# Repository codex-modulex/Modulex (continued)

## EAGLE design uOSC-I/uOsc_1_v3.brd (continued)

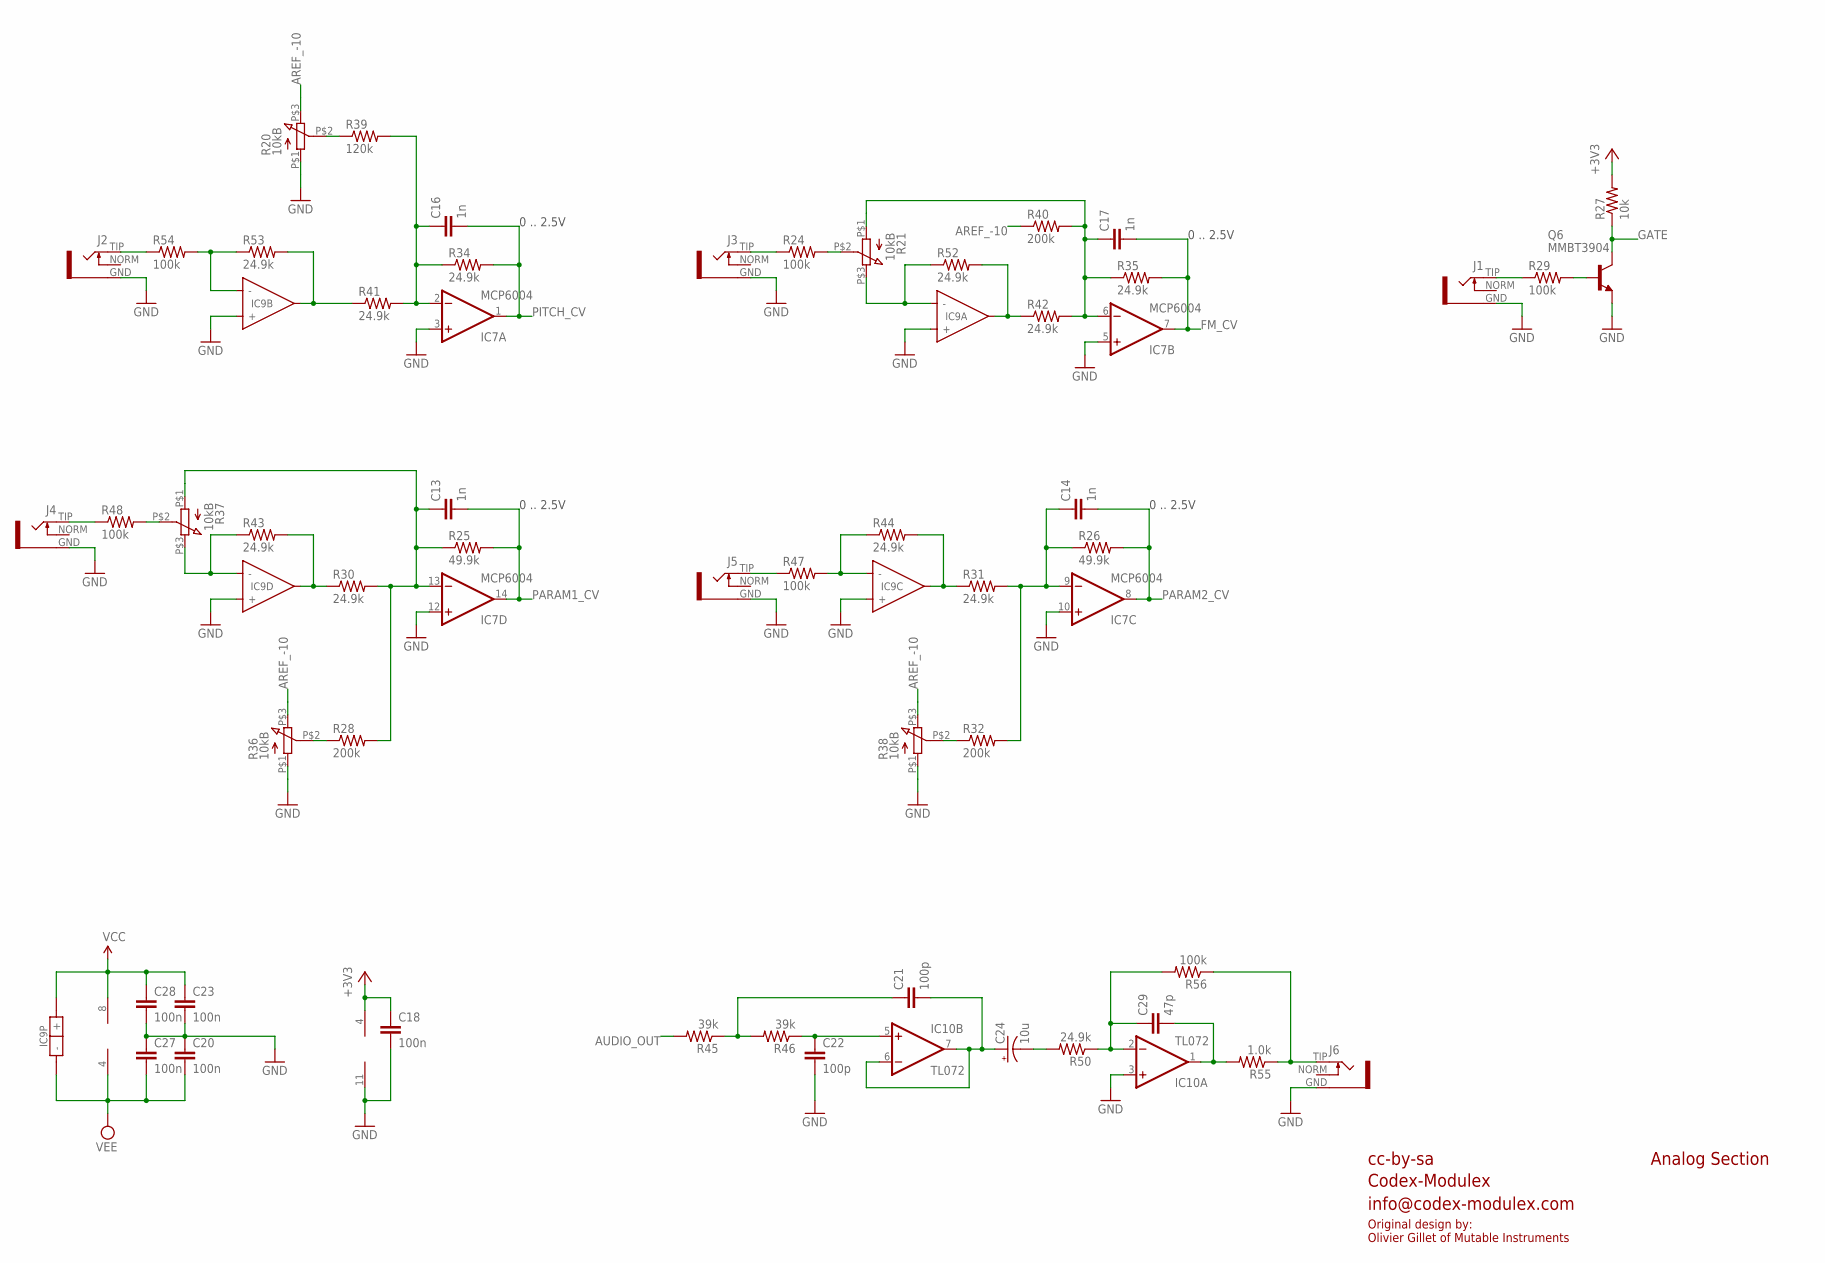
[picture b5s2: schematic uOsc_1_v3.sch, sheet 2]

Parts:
C13, C14, C16, C17: 1n; PARTS_AMAN_RESISTOR_0603
C18, C20, C23, C27, C28: 100n; PARTS_AMAN_RESISTOR_0603
C21, C22: 100p; PARTS_AMAN_RESISTOR_0603
C24: 10u; PANASONIC_B
C29: 47p; PARTS_AMAN_RESISTOR_0603
IC7: MCP6004; SO14
IC9: TL074; UBRAIDS_SE_TSSOP-14
IC10: TL072; SO08
J1, J2, J3, J4, J5, J6: S_JACK_S2_INV
Q6: MMBT3904; SOT23-BEC
R20, R21, R36, R37, R38: 10kB; Q-POT2
R24, R29, R47, R48, R54, R56: 100k; PARTS_AMAN_RESISTOR_0603
R25, R26: 49.9k; PARTS_AMAN_RESISTOR_0603
R27: 10k; PARTS_AMAN_RESISTOR_0603
R28, R32, R40: 200k; PARTS_AMAN_RESISTOR_0603
R30, R31, R34, R35, R41, R42, R43, R44, R50, R52, R53: 24.9k; PARTS_AMAN_RESISTOR_0603
R39: 120k; PARTS_AMAN_RESISTOR_0603
R45, R46: 39k; PARTS_AMAN_RESISTOR_0603
R55: 1.0k; PARTS_AMAN_RESISTOR_0603

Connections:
+3V3: C18.1, IC7.4 (V+), R27.2; also elsewhere on the board
AREF_-10: R20.P$3 (3), R36.P$3 (3), R38.P$3 (3), R40.1; also elsewhere on the board
AUDIO_OUT: R45.2; also elsewhere on the board
FM_CV: C17.2, IC7.7 (OUT), R35.2; also elsewhere on the board
GATE: Q6.C, R27.1; also elsewhere on the board
GND: C18.2, C20.1, C22.2, C23.2, C27.1, C28.2, IC7.3 (+IN), IC7.5 (+IN), IC7.10 (+IN), IC7.11 (V-), IC7.12 (+IN), IC9.3 (+), IC9.5 (+), IC9.10 (+), IC9.12 (+), IC10.3 (+IN), J1.GND, J2.GND, J3.GND, J4.GND, J5.GND, J6.GND, Q6.E, R20.P$1 (1), R36.P$1 (1), R38.P$1 (1); also elsewhere on the board
unnamed: IC9.7 (OUT), R41.1, R53.2
unnamed: R20.P$2 (2), R39.1
unnamed: J2.TIP, R54.1
unnamed: C16.1, IC7.2 (-IN), R34.1, R39.2, R41.2
unnamed: IC9.6 (-), R53.1, R54.2
unnamed: J3.TIP, R24.1
unnamed: J4.TIP, R48.1
unnamed: R21.P$2 (2), R24.2
unnamed: IC9.13 (-), R37.P$3 (3), R43.1
unnamed: IC9.14 (OUT), R30.1, R43.2
unnamed: IC9.2 (-), R21.P$3 (3), R52.1
unnamed: IC9.1 (OUT), R42.1, R52.2
unnamed: C17.1, IC7.6 (-IN), R21.P$1 (1), R35.1, R40.2, R42.2
unnamed: J1.TIP, R29.1
unnamed: IC9.8 (OUT), R31.1, R44.2
unnamed: C13.1, IC7.13 (-IN), R25.1, R28.2, R30.2, R37.P$1 (1)
unnamed: J5.TIP, R47.1
unnamed: R28.1, R36.P$2 (2)
unnamed: R37.P$2 (2), R48.2
unnamed: IC9.9 (-), R44.1, R47.2
unnamed: R32.1, R38.P$2 (2)
unnamed: Q6.B, R29.2
unnamed: C21.2, C24.+, IC10.6 (-IN), IC10.7 (OUT)
unnamed: C24.-, R50.2
unnamed: C22.1, IC10.5 (+IN), R46.1
unnamed: C14.1, IC7.9 (-IN), R26.1, R31.2, R32.2
unnamed: C21.1, R45.1, R46.2
unnamed: J6.TIP, R55.1, R56.1
unnamed: C29.2, IC10.1 (OUT), R55.2
unnamed: C29.1, IC10.2 (-IN), R50.1, R56.2
PARAM1_CV: C13.2, IC7.14 (OUT), R25.2; also elsewhere on the board
PARAM2_CV: C14.2, IC7.8 (OUT), R26.2; also elsewhere on the board
PITCH_CV: C16.2, IC7.1 (OUT), R34.2; also elsewhere on the board
VCC: C23.1, C28.1, IC9.4 (+), IC10.8 (V+); also elsewhere on the board
VEE: C20.2, C27.2, IC9.11 (-), IC10.4 (V-); also elsewhere on the board

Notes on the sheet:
cc-by-sa
Codex-Modulex
info@codex-modulex.com
Analog Section
0 .. 2.5V
Original design by: Olivier Gillet of Mutable Instruments

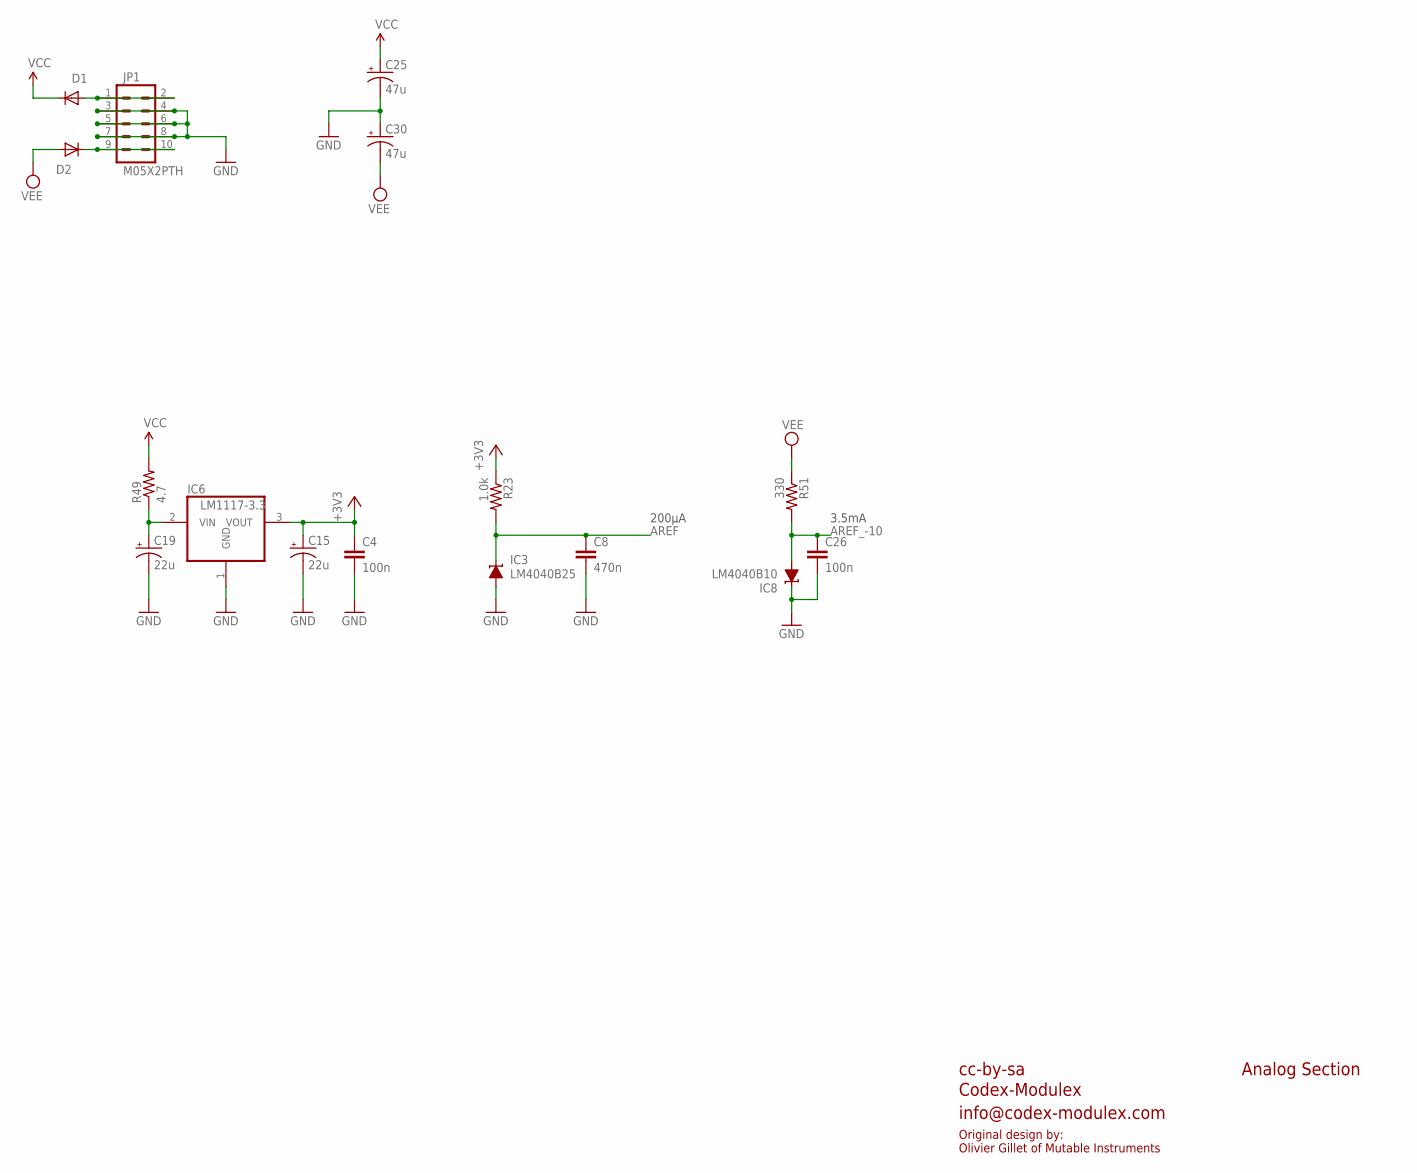
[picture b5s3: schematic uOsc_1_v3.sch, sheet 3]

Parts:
C4, C26: 100n; PARTS_AMAN_RESISTOR_0603
C8: 470n; PARTS_AMAN_RESISTOR_0603
C15, C19: 22u; PANASONIC_C
C25, C30: 47u; PANASONIC_D
D1, D2: 1N5819HW; SOD123
IC3: LM4040B25; DBZ_R-PDSO-G3
IC6: LM1117-3.3; TO252
IC8: LM4040B10; DBZ_R-PDSO-G3
JP1: M05X2PTH; AVR_ICSP
R23: 1.0k; PARTS_AMAN_RESISTOR_0603
R49: 4.7; R1206
R51: 330; PARTS_AMAN_RESISTOR_0603

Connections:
+3V3: C4.1, C15.+, IC6.3 (VOUT), R23.1; also elsewhere on the board
AREF: C8.1, IC3.1 (C), R23.2; also elsewhere on the board
AREF_-10: C26.1, IC8.2 (A), R51.2; also elsewhere on the board
GND: C4.2, C8.2, C15.-, C19.-, C25.-, C26.2, C30.+, IC3.2 (A), IC6.1 (GND), IC8.1 (C), JP1.3, JP1.4, JP1.5, JP1.6, JP1.7, JP1.8; also elsewhere on the board
unnamed: C19.+, IC6.2 (VIN), R49.1
unnamed: D1.A, JP1.1, JP1.2
unnamed: D2.C, JP1.9, JP1.10
VCC: C25.+, D1.C, R49.2; also elsewhere on the board
VEE: C30.-, D2.A, R51.1; also elsewhere on the board

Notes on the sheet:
3.5mA
200µA
cc-by-sa
Codex-Modulex
info@codex-modulex.com
Analog Section
Original design by: Olivier Gillet of Mutable Instruments

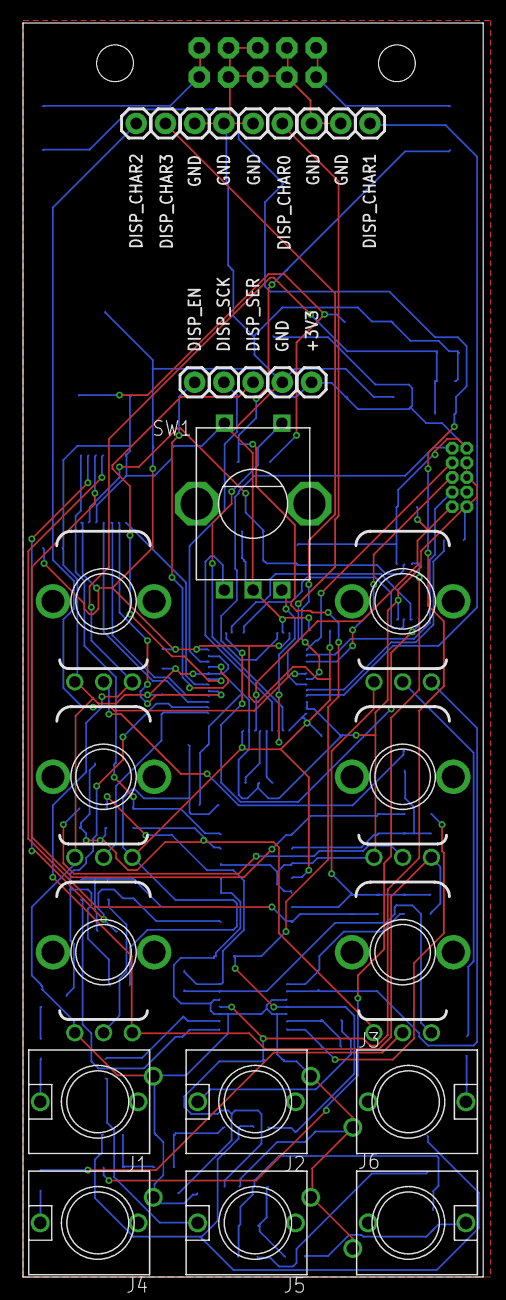
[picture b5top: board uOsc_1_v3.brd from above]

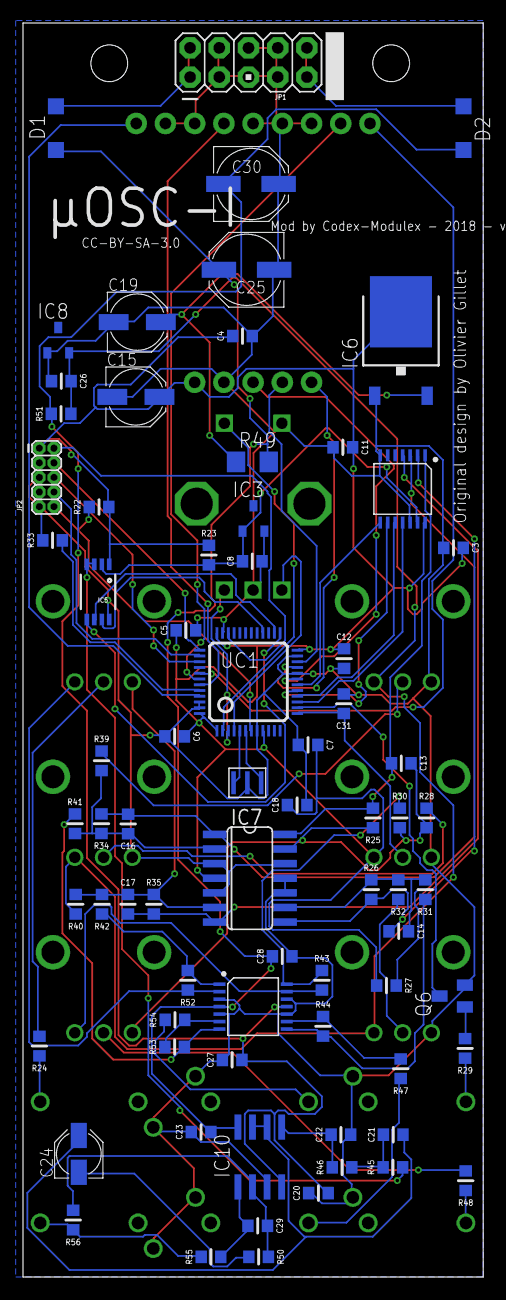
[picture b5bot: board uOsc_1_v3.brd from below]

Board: 2 copper layers, 40.0 x 109.0 mm, 101 parts (74 on the bottom side), 71 nets.

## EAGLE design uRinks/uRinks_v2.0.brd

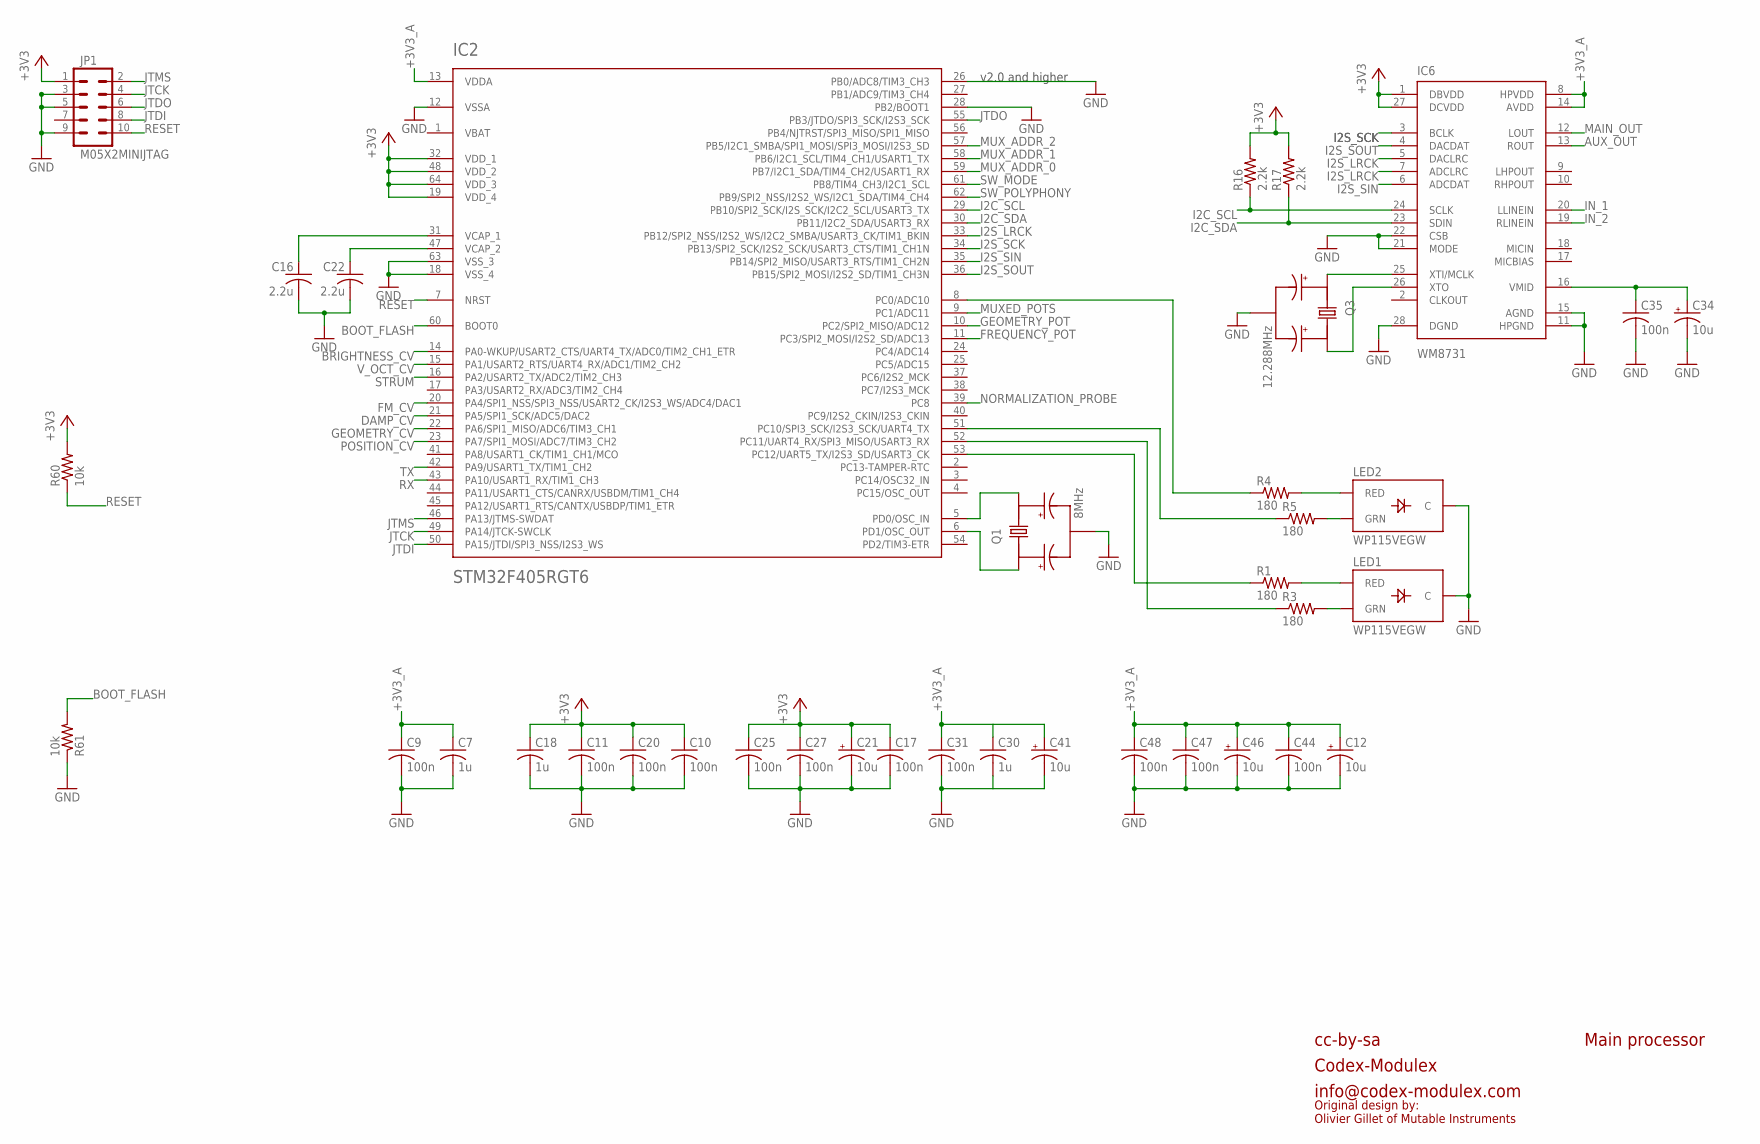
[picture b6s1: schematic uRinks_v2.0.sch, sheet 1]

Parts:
C7, C18, C30: 1u; C0603
C9, C10, C11, C17, C20, C25, C27, C31, C35, C44, C47, C48: 100n; C0603
C12, C21, C34, C41, C46: 10u; PANASONIC_A
C16, C22: 2.2u; C0805
IC2: STM32F405RGT6; TQFP-10X10-64
IC6: WM8731; SSOP28
JP1: M05X2MINIJTAG; 2X5-1.27
LED1, LED2: WP115VEGW; LED-BICOLOR-THROUGHHOLE
Q1: 8MHz; INSTRUO_CRYSTAL_SMALLER
Q3: 12.288MHz; INSTRUO_CRYSTAL_SMALLER
R1, R3, R4, R5: 180; R0603
R16, R17: 2.2k; R0603
R60, R61: 10k; R0603

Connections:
+3V3: C10.1, C11.1, C17.1, C18.1, C20.1, C21.+, C25.1, C27.1, IC2.19 (VDD_4), IC2.32 (VDD_1), IC2.48 (VDD_2), IC2.64 (VDD_3), IC6.1 (DBVDD), IC6.27 (DCVDD), JP1.1, R16.2, R17.2, R60.2; also elsewhere on the board
+3V3_A: C7.1, C9.1, C12.+, C30.1, C31.1, C41.+, C44.1, C46.+, C47.1, C48.1, IC2.13 (VDDA), IC6.8 (HPVDD), IC6.14 (AVDD); also elsewhere on the board
AUX_OUT: IC6.13 (ROUT); also elsewhere on the board
BOOT_FLASH: IC2.60 (BOOT0), R61.2
BRIGHTNESS_CV: IC2.14 (PA0-WKUP/USART2_CTS/UART4_TX/ADC0/TIM2_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); also elsewhere on the board
DAMP_CV: IC2.21 (PA5/SPI1_SCK/ADC5/DAC2); also elsewhere on the board
FM_CV: IC2.20 (PA4/SPI1_NSS/SPI3_NSS/USART2_CK/I2S3_WS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); also elsewhere on the board
FREQUENCY_POT: IC2.11 (PC3/SPI2_MOSI/I2S2_SD/ADC13); also elsewhere on the board
GEOMETRY_CV: IC2.22 (PA6/SPI1_MISO/ADC6/TIM3_CH1); also elsewhere on the board
GEOMETRY_POT: IC2.10 (PC2/SPI2_MISO/ADC12); also elsewhere on the board
GND: C7.2, C9.2, C10.2, C11.2, C12.-, C16.2, C17.2, C18.2, C20.2, C21.-, C22.2, C25.2, C27.2, C30.2, C31.2, C34.-, C35.2, C41.-, C44.2, C46.-, C47.2, C48.2, IC2.12 (VSSA), IC2.18 (VSS_4), IC2.26 (PB0/ADC8/TIM3_CH3), IC2.28 (PB2/BOOT1), IC2.63 (VSS_3), IC6.11 (HPGND), IC6.15 (AGND), IC6.21 (MODE), IC6.22 (CSB), IC6.28 (DGND), JP1.3, JP1.5, JP1.9, LED1.2 (C), LED2.2 (C), Q1.GND, Q3.GND, R61.1; also elsewhere on the board
I2C_SCL: IC2.29 (PB10/SPI2_SCK/I2S_SCK/I2C2_SCL/USART3_TX), IC6.24 (SCLK), R16.1
I2C_SDA: IC2.30 (PB11/I2C2_SDA/USART3_RX), IC6.23 (SDIN), R17.1
I2S_LRCK: IC2.33 (PB12/SPI2_NSS/I2S2_WS/I2C2_SMBA/USART3_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), IC6.5 (DACLRC), IC6.7 (ADCLRC)
I2S_SCK: IC2.34 (PB13/SPI2_SCK/I2S2_SCK/USART3_CTS/TIM1_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), IC6.3 (BCLK)
I2S_SIN: IC2.35 (PB14/SPI2_MISO/USART3_RTS/TIM1_CH2N), IC6.6 (ADCDAT)
I2S_SOUT: IC2.36 (PB15/SPI2_MOSI/I2S2_SD/TIM1_CH3N), IC6.4 (DACDAT)
IN_1: IC6.20 (LLINEIN); also elsewhere on the board
IN_2: IC6.19 (RLINEIN); also elsewhere on the board
JTCK: IC2.49 (PA14/JTCK-SWCLK), JP1.4
JTDI: IC2.50 (PA15/JTDI/SPI3_NSS/I2S3_WS), JP1.8
JTDO: IC2.55 (PB3/JTDO/SPI3_SCK/I2S3_SCK), JP1.6
JTMS: IC2.46 (PA13/JTMS-SWDAT), JP1.2
MAIN_OUT: IC6.12 (LOUT); also elsewhere on the board
MUXED_POTS: IC2.9 (PC1/ADC11); also elsewhere on the board
MUX_ADDR_0: IC2.59 (PB7/I2C1_SDA/TIM4_CH2/USART1_RX); also elsewhere on the board
MUX_ADDR_1: IC2.58 (PB6/I2C1_SCL/TIM4_CH1/USART1_TX); also elsewhere on the board
MUX_ADDR_2: IC2.57 (PB5/I2C1_SMBA/SPI1_MOSI/SPI3_MOSI/I2S3_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); also elsewhere on the board
unnamed: IC2.6 (PD1/OSC_OUT), Q1.X1
unnamed: IC2.5 (PD0/OSC_IN), Q1.X2
unnamed: LED1.3 (RED), R1.2
unnamed: C22.1, IC2.47 (VCAP_2)
unnamed: C34.+, C35.1, IC6.16 (VMID)
unnamed: C16.1, IC2.31 (VCAP_1)
unnamed: LED1.1 (GRN), R3.2
unnamed: LED2.3 (RED), R4.2
unnamed: LED2.1 (GRN), R5.2
unnamed: IC2.52 (PC11/UART4_RX/SPI3_MISO/USART3_RX), R3.1
unnamed: IC2.8 (PC0/ADC10), R4.1
unnamed: IC6.25 (XTI/MCLK), Q3.X1
unnamed: IC6.26 (XTO), Q3.X2
unnamed: IC2.53 (PC12/UART5_TX/I2S3_SD/USART3_CK), R1.1
unnamed: IC2.51 (PC10/SPI3_SCK/I2S3_SCK/UART4_TX), R5.1
NORMALIZATION_PROBE: IC2.39 (PC8); also elsewhere on the board
POSITION_CV: IC2.23 (PA7/SPI1_MOSI/ADC7/TIM3_CH2); also elsewhere on the board
RESET: IC2.7 (NRST), JP1.10, R60.1
RX: IC2.43 (PA10/USART1_RX/TIM1_CH3)
STRUM: IC2.16 (PA2/USART2_TX/ADC2/TIM2_CH3); also elsewhere on the board
SW_MODE: IC2.61 (PB8/TIM4_CH3/I2C1_SCL); also elsewhere on the board
SW_POLYPHONY: IC2.62 (PB9/SPI2_NSS/I2S2_WS/I2C1_SDA/TIM4_CH4); also elsewhere on the board
TX: IC2.42 (PA9/USART1_TX/TIM1_CH2)
VBAT: IC2.1 (VBAT)
V_OCT_CV: IC2.15 (PA1/USART2_RTS/UART4_RX/ADC1/TIM2_CH2); also elsewhere on the board

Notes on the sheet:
cc-by-sa
Codex-Modulex
info@codex-modulex.com
Main processor
v2.0 and higher
Original design by: Olivier Gillet of Mutable Instruments

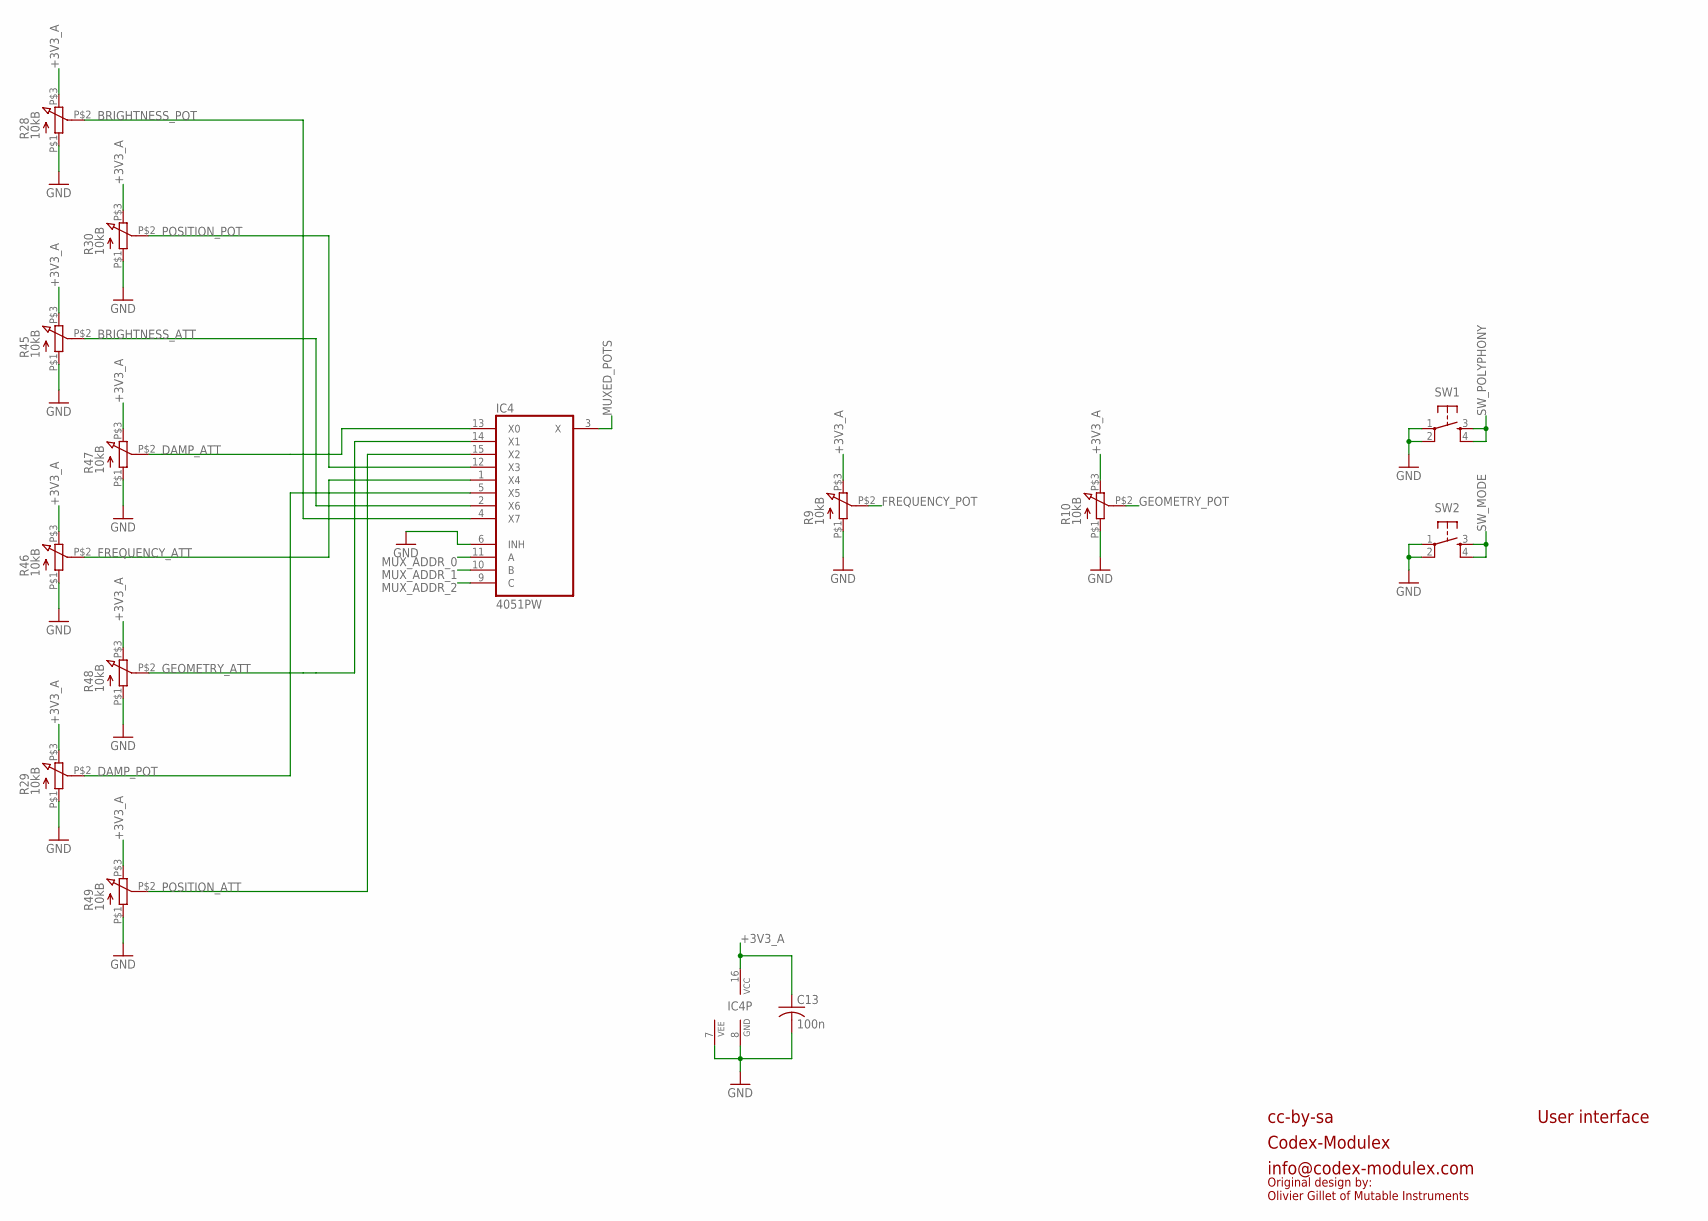
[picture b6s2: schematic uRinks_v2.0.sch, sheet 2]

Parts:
C13: 100n; C0603
IC4: 4051PW; TSSOP16
R9, R10, R28, R29, R30, R45, R46, R47, R48, R49: 10kB; INSTRUO_Q-POT2
SW1, SW2: TAC_SWITCHPTH; TACTILE-PTH

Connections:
+3V3_A: C13.1, IC4.16 (VCC), R9.P$3 (3), R10.P$3 (3), R28.P$3 (3), R29.P$3 (3), R30.P$3 (3), R45.P$3 (3), R46.P$3 (3), R47.P$3 (3), R48.P$3 (3), R49.P$3 (3); also elsewhere on the board
BRIGHTNESS_ATT: IC4.2 (X6), R45.P$2 (2)
BRIGHTNESS_POT: IC4.4 (X7), R28.P$2 (2)
DAMP_ATT: IC4.13 (X0), R47.P$2 (2)
DAMP_POT: IC4.5 (X5), R29.P$2 (2)
FREQUENCY_ATT: IC4.1 (X4), R46.P$2 (2)
FREQUENCY_POT: R9.P$2 (2); also elsewhere on the board
GEOMETRY_ATT: IC4.14 (X1), R48.P$2 (2)
GEOMETRY_POT: R10.P$2 (2); also elsewhere on the board
GND: C13.2, IC4.6 (INH), IC4.7 (VEE), IC4.8 (GND), R9.P$1 (1), R10.P$1 (1), R28.P$1 (1), R29.P$1 (1), R30.P$1 (1), R45.P$1 (1), R46.P$1 (1), R47.P$1 (1), R48.P$1 (1), R49.P$1 (1), SW1.1, SW1.2, SW2.1, SW2.2; also elsewhere on the board
MUXED_POTS: IC4.3 (X); also elsewhere on the board
MUX_ADDR_0: IC4.11 (A); also elsewhere on the board
MUX_ADDR_1: IC4.10 (B); also elsewhere on the board
MUX_ADDR_2: IC4.9 (C); also elsewhere on the board
POSITION_ATT: IC4.15 (X2), R49.P$2 (2)
POSITION_POT: IC4.12 (X3), R30.P$2 (2)
SW_MODE: SW2.3, SW2.4; also elsewhere on the board
SW_POLYPHONY: SW1.3, SW1.4; also elsewhere on the board

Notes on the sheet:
cc-by-sa
Codex-Modulex
info@codex-modulex.com
User interface
Original design by: Olivier Gillet of Mutable Instruments

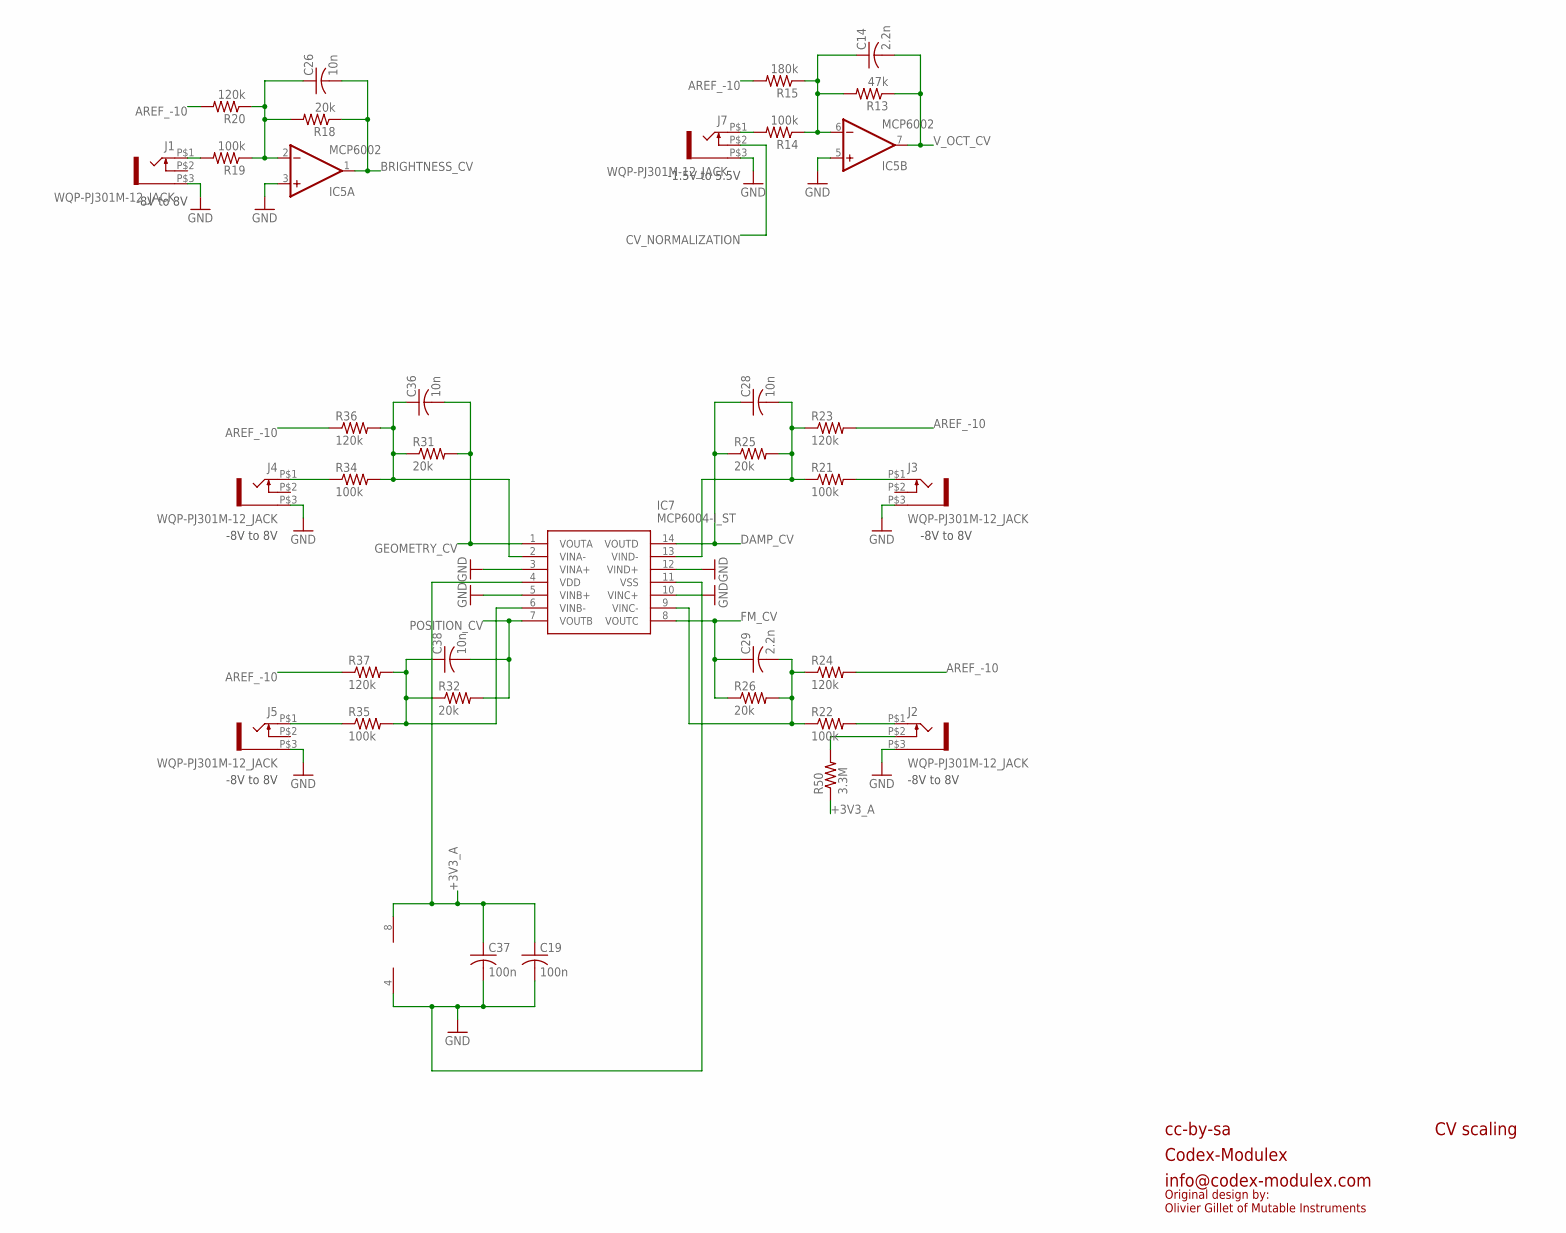
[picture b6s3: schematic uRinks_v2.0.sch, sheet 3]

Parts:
C14, C29: 2.2n; C0603
C19, C37: 100n; C0603
C26, C28, C36, C38: 10n; C0603
IC5: MCP6002; SO08
IC7: MCP6004-I_ST; SOP65P640X120-14N
J1, J2, J3, J4, J5, J7: WQP-PJ301M-12_JACK
R13: 47k; R0603
R14, R19, R21, R22, R34, R35: 100k; R0603
R15: 180k; R0603
R18, R25, R26, R31, R32: 20k; R0603
R20, R23, R24, R36, R37: 120k; R0603
R50: 3.3M; R0603

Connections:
+3V3_A: C19.1, C37.1, IC5.8 (V+), IC7.4 (VDD), R50.1; also elsewhere on the board
AREF_-10: R15.2, R20.2, R23.2, R24.2, R36.1, R37.1; also elsewhere on the board
BRIGHTNESS_CV: C26.2, IC5.1 (OUT), R18.1; also elsewhere on the board
CV_NORMALIZATION: J7.P$2 (3); also elsewhere on the board
DAMP_CV: C28.1, IC7.14 (VOUTD), R25.1; also elsewhere on the board
FM_CV: C29.1, IC7.8 (VOUTC), R26.1; also elsewhere on the board
GEOMETRY_CV: C36.2, IC7.1 (VOUTA), R31.2; also elsewhere on the board
GND: C19.2, C37.2, IC5.3 (+IN), IC5.4 (V-), IC5.5 (+IN), IC7.3 (VINA+), IC7.5 (VINB+), IC7.10 (VINC+), IC7.11 (VSS), IC7.12 (VIND+), J1.P$3 (1), J2.P$3 (1), J3.P$3 (1), J4.P$3 (1), J5.P$3 (1), J7.P$3 (1); also elsewhere on the board
unnamed: J1.P$1 (2), R19.2
unnamed: C26.1, IC5.2 (-IN), R18.2, R19.1, R20.1
unnamed: J7.P$1 (2), R14.2
unnamed: J3.P$1 (2), R21.2
unnamed: J2.P$1 (2), R22.2
unnamed: C29.2, IC7.9 (VINC-), R22.1, R24.1, R26.2
unnamed: C14.1, IC5.6 (-IN), R13.2, R14.1, R15.1
unnamed: C28.2, IC7.13 (VIND-), R21.1, R23.1, R25.2
unnamed: J4.P$1 (2), R34.1
unnamed: C36.1, IC7.2 (VINA-), R31.1, R34.2, R36.2
unnamed: J5.P$1 (2), R35.1
unnamed: C38.1, IC7.6 (VINB-), R32.1, R35.2, R37.2
unnamed: J2.P$2 (3), R50.2
POSITION_CV: C38.2, IC7.7 (VOUTB), R32.2; also elsewhere on the board
V_OCT_CV: C14.2, IC5.7 (OUT), R13.1; also elsewhere on the board

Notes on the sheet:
cc-by-sa
Codex-Modulex
info@codex-modulex.com
CV scaling
-8V to 8V
-1.5V to 5.5V
Original design by: Olivier Gillet of Mutable Instruments

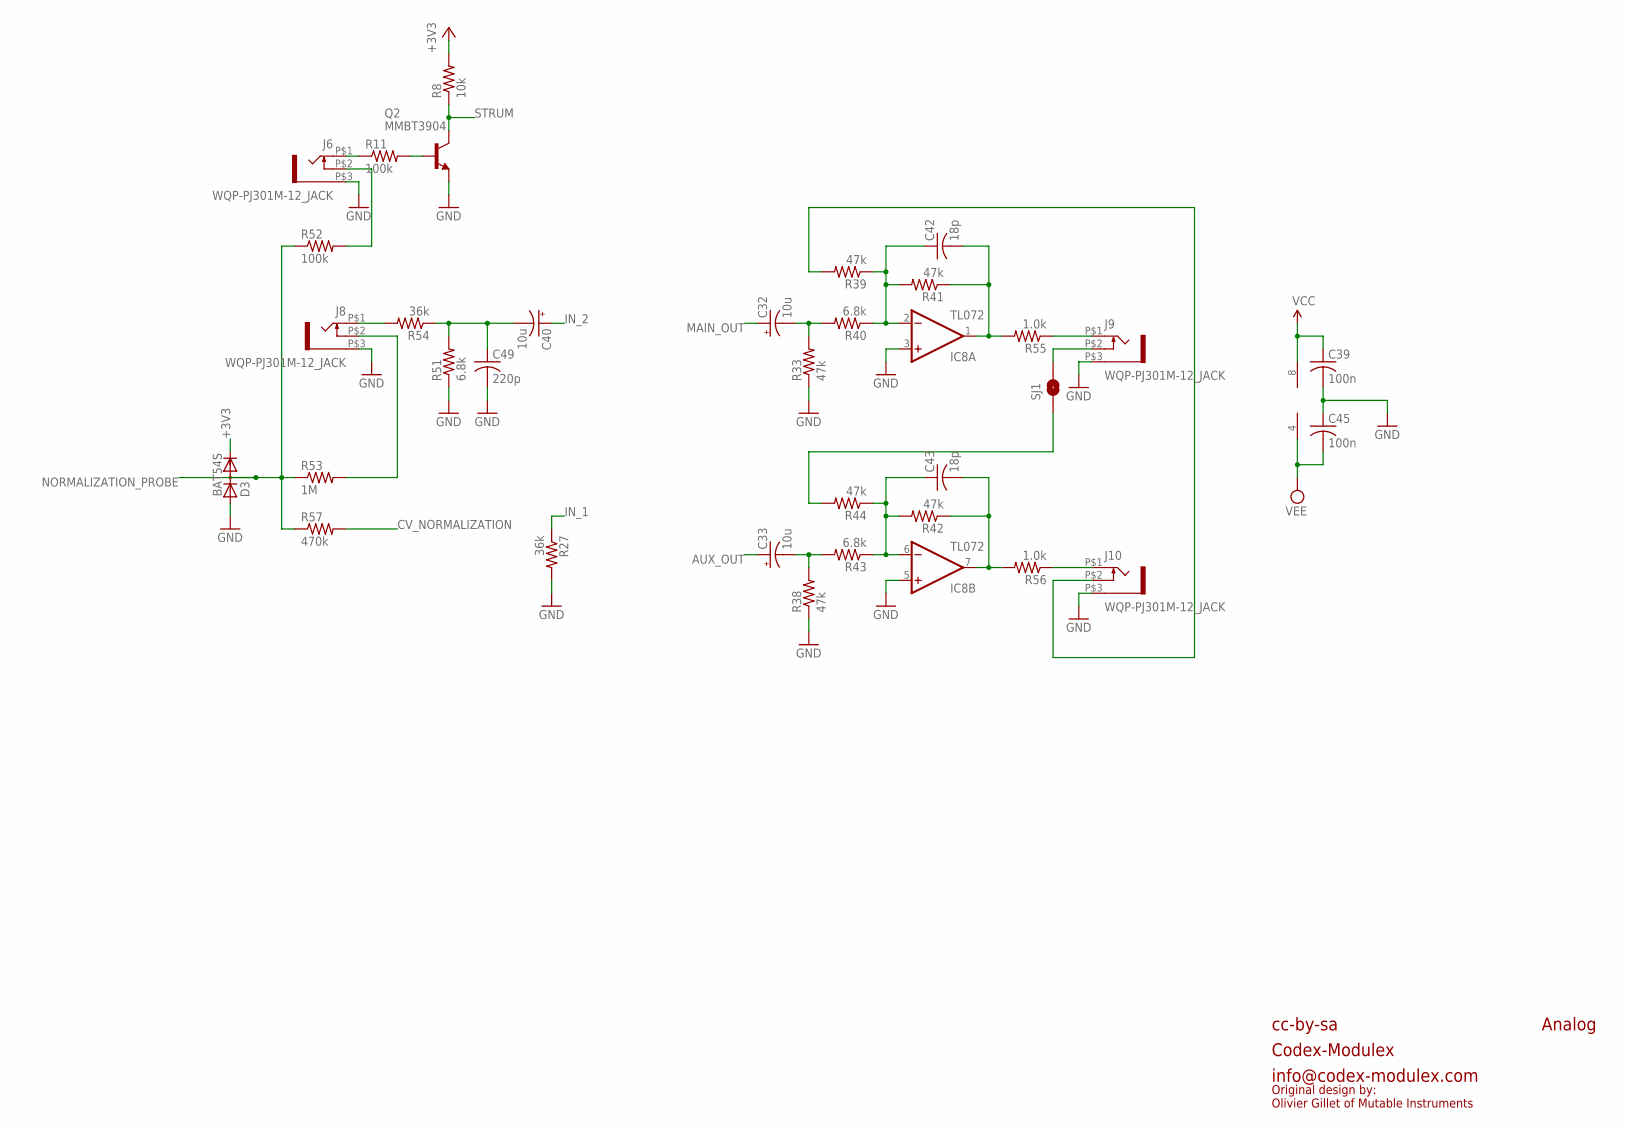
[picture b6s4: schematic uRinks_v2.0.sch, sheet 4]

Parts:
C32, C33, C40: 10u; PANASONIC_A
C39, C45: 100n; C0603
C42, C43: 18p; C0603
C49: 220p; C0603
D3: BAT54S; SOT23
IC8: TL072; SO08
J6, J8, J9, J10: WQP-PJ301M-12_JACK
Q2: MMBT3904; SOT23-BEC
R8: 10k; R0603
R11, R52: 100k; R0603
R27, R54: 36k; R0603
R33, R38, R39, R41, R42, R44: 47k; R0603
R40, R43, R51: 6.8k; R0603
R53: 1M; R0603
R55, R56: 1.0k; R0603
R57: 470k; R0603
SJ1: SOLDERJUMPERNC2; SJ_2S-NOTRACE

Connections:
+3V3: D3.2 (C), R8.2; also elsewhere on the board
AUX_OUT: C33.+; also elsewhere on the board
CV_NORMALIZATION: R57.2; also elsewhere on the board
GND: C39.2, C45.1, C49.2, D3.1 (A), IC8.3 (+IN), IC8.5 (+IN), J6.P$3 (1), J8.P$3 (1), J9.P$3 (1), J10.P$3 (1), Q2.E, R27.2, R33.1, R38.1, R51.1; also elsewhere on the board
IN_1: R27.1; also elsewhere on the board
IN_2: C40.+; also elsewhere on the board
MAIN_OUT: C32.+; also elsewhere on the board
unnamed: J6.P$1 (2), R11.1
unnamed: C40.-, C49.1, R51.2, R54.1
unnamed: J6.P$2 (3), R52.2
unnamed: J8.P$1 (2), R54.2
unnamed: C33.-, R38.2, R43.2
unnamed: C43.1, IC8.6 (-IN), R42.2, R43.1, R44.1
unnamed: C43.2, IC8.7 (OUT), R42.1, R56.2
unnamed: J10.P$1 (2), R56.1
unnamed: C32.-, R33.2, R40.2
unnamed: C42.1, IC8.2 (-IN), R39.1, R40.1, R41.2
unnamed: C42.2, IC8.1 (OUT), R41.1, R55.2
unnamed: J9.P$1 (2), R55.1
unnamed: J8.P$2 (3), R53.2
unnamed: J10.P$2 (3), R39.2
unnamed: R44.2, SJ1.1
unnamed: J9.P$2 (3), SJ1.2
unnamed: Q2.B, R11.2
NORMALIZATION_PROBE: D3.3 (AC), R52.1, R53.1, R57.1; also elsewhere on the board
STRUM: Q2.C, R8.1; also elsewhere on the board
VCC: C39.1, IC8.8 (V+); also elsewhere on the board
VEE: C45.2, IC8.4 (V-); also elsewhere on the board

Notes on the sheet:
cc-by-sa
Codex-Modulex
info@codex-modulex.com
Analog
Original design by: Olivier Gillet of Mutable Instruments
